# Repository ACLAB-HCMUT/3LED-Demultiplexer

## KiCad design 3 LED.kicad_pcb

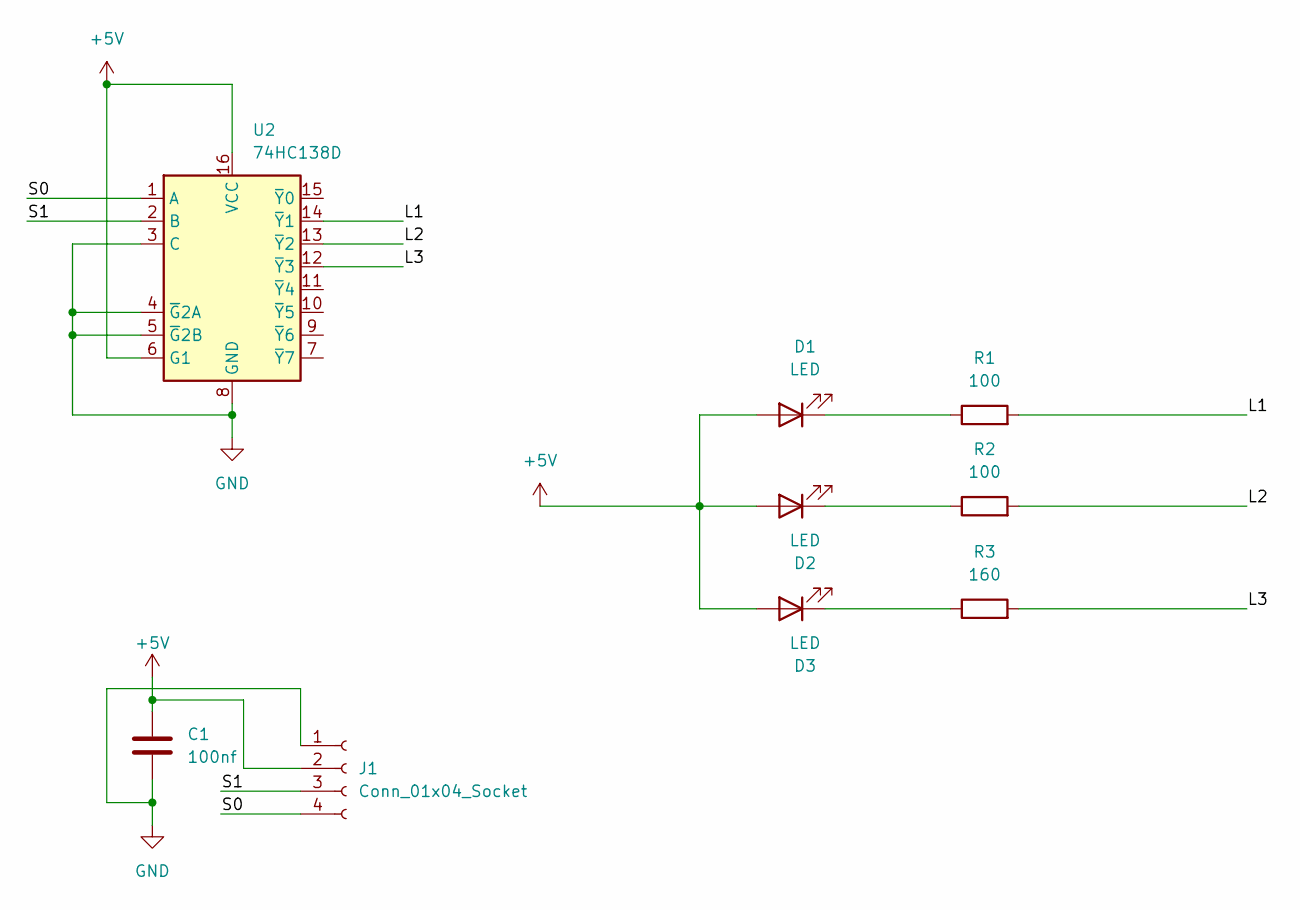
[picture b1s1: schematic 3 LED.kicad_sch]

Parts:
C1: 100nf; C_0805_2012Metric
D1, D2, D3: LED; LED_D10.0mm
J1: Conn_01x04_Socket; SEEEDSTUDIO_114020164
R1, R2: 100; R_0603_1608Metric
R3: 160; R_0603_1608Metric
U2: 74HC138D; SOP-16_3.9x9.9mm_P1.27mm

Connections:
+5V: C1.1, D1.2 (A), D2.2 (A), D3.2 (A), J1.2, U2.6 (G1), U2.16 (VCC)
/L1: R1.2, U2.14 (~Y1)
/L2: R2.2, U2.13 (~Y2)
/L3: R3.2, U2.12 (~Y3)
/S0: J1.4, U2.1 (A)
/S1: J1.3, U2.2 (B)
GND: C1.2, J1.1, U2.3 (C), U2.4 (~G2A), U2.5 (~G2B), U2.8 (GND)
unnamed: D1.1 (K), R1.1
unnamed: D2.1 (K), R2.1
unnamed: D3.1 (K), R3.1

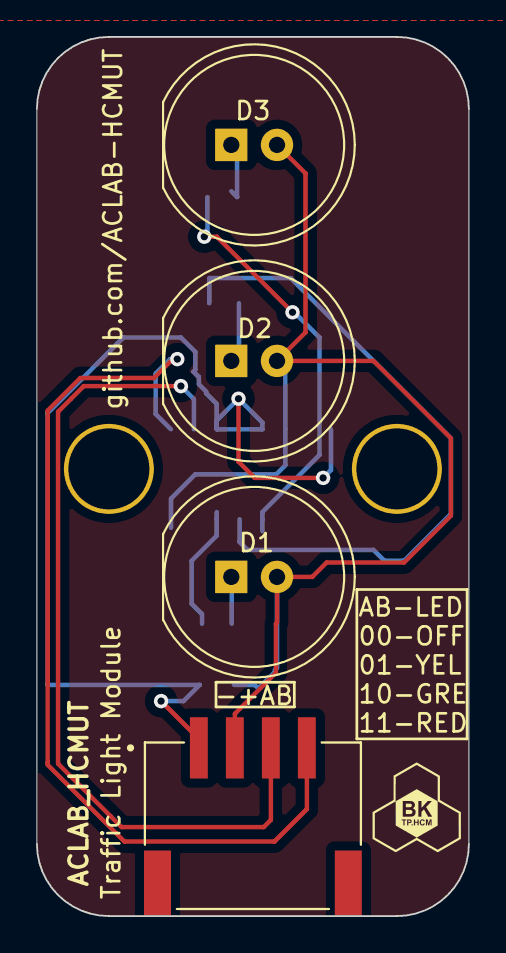
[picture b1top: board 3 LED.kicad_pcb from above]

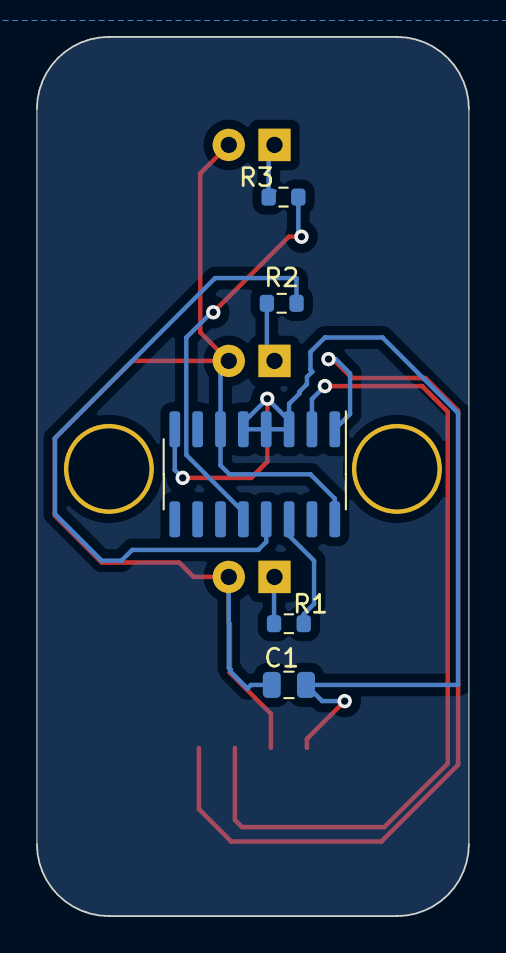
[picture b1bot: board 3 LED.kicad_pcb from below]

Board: 2 copper layers, 24.0 x 48.8 mm, 9 parts (5 on the bottom side), 10 nets.

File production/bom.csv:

Designator,Footprint,Quantity,Value,LCSC Part #
C1,0805,1,100nf,
"D1, D2, D3",LED_D10.0mm,3,LED,
J1,SEEEDSTUDIO_114020164,1,Conn_01x04_Socket,
"R1, R2",0603,2,100,
R3,0603,1,160,
U2,SOP-16_3.9x9.9mm_P1.27mm,1,74HC138D,

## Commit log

2024-05-06 On Production
2024-06-01 update Schematic
2024-06-02 Production V2
2024-06-02 Production Version
2024-09-09 update: 74HC138D
2024-09-10 update label
